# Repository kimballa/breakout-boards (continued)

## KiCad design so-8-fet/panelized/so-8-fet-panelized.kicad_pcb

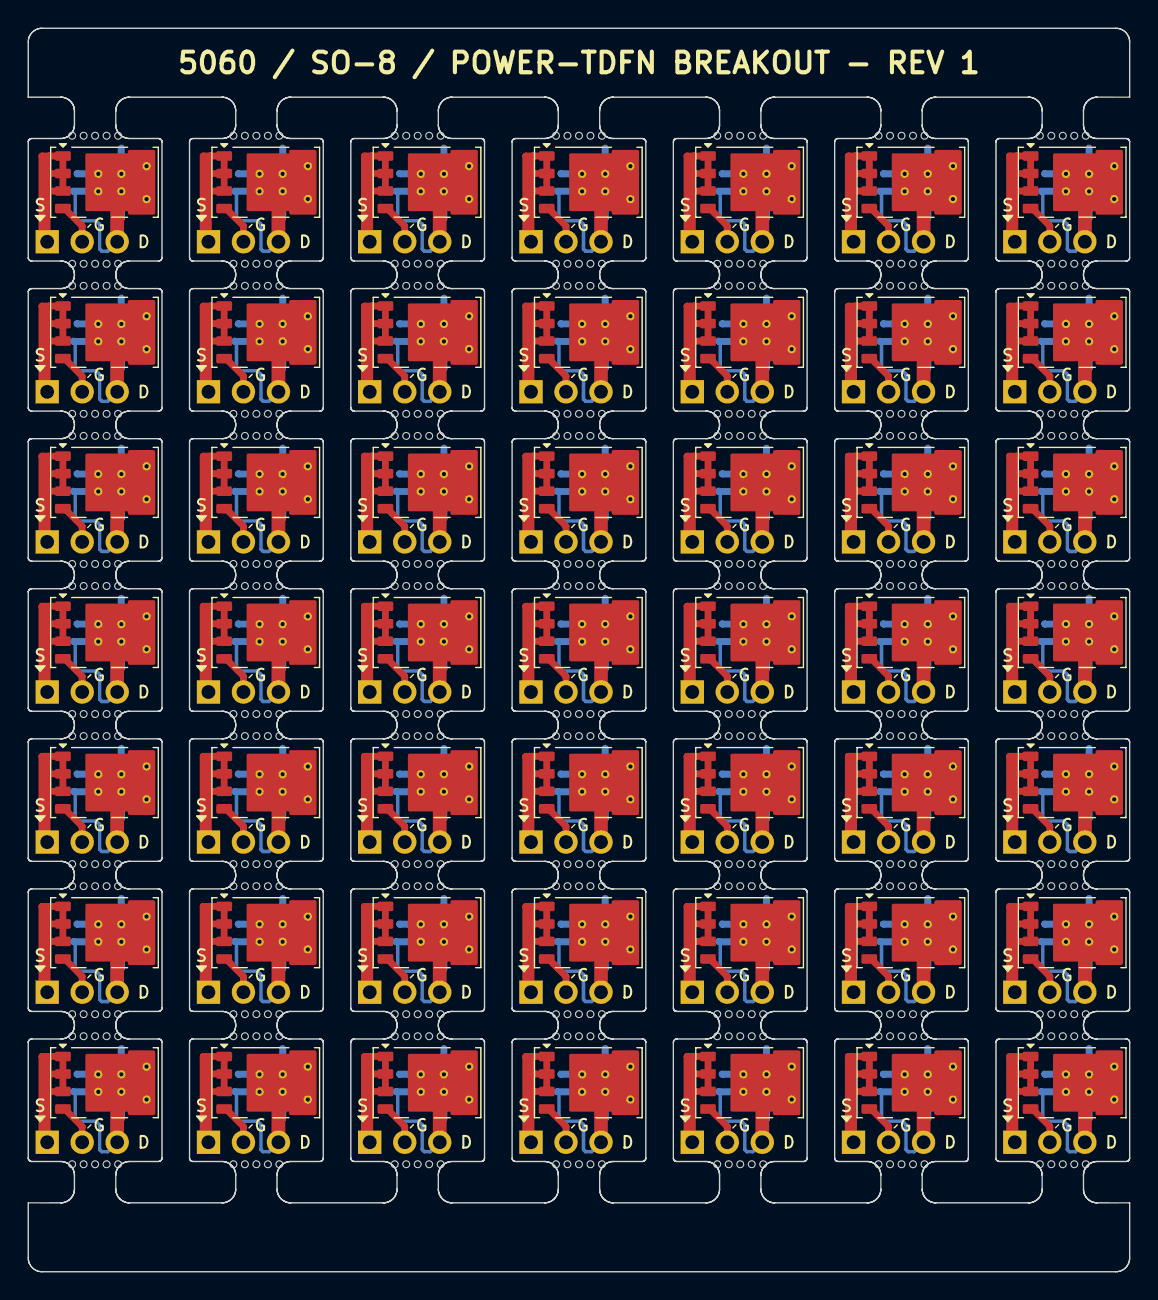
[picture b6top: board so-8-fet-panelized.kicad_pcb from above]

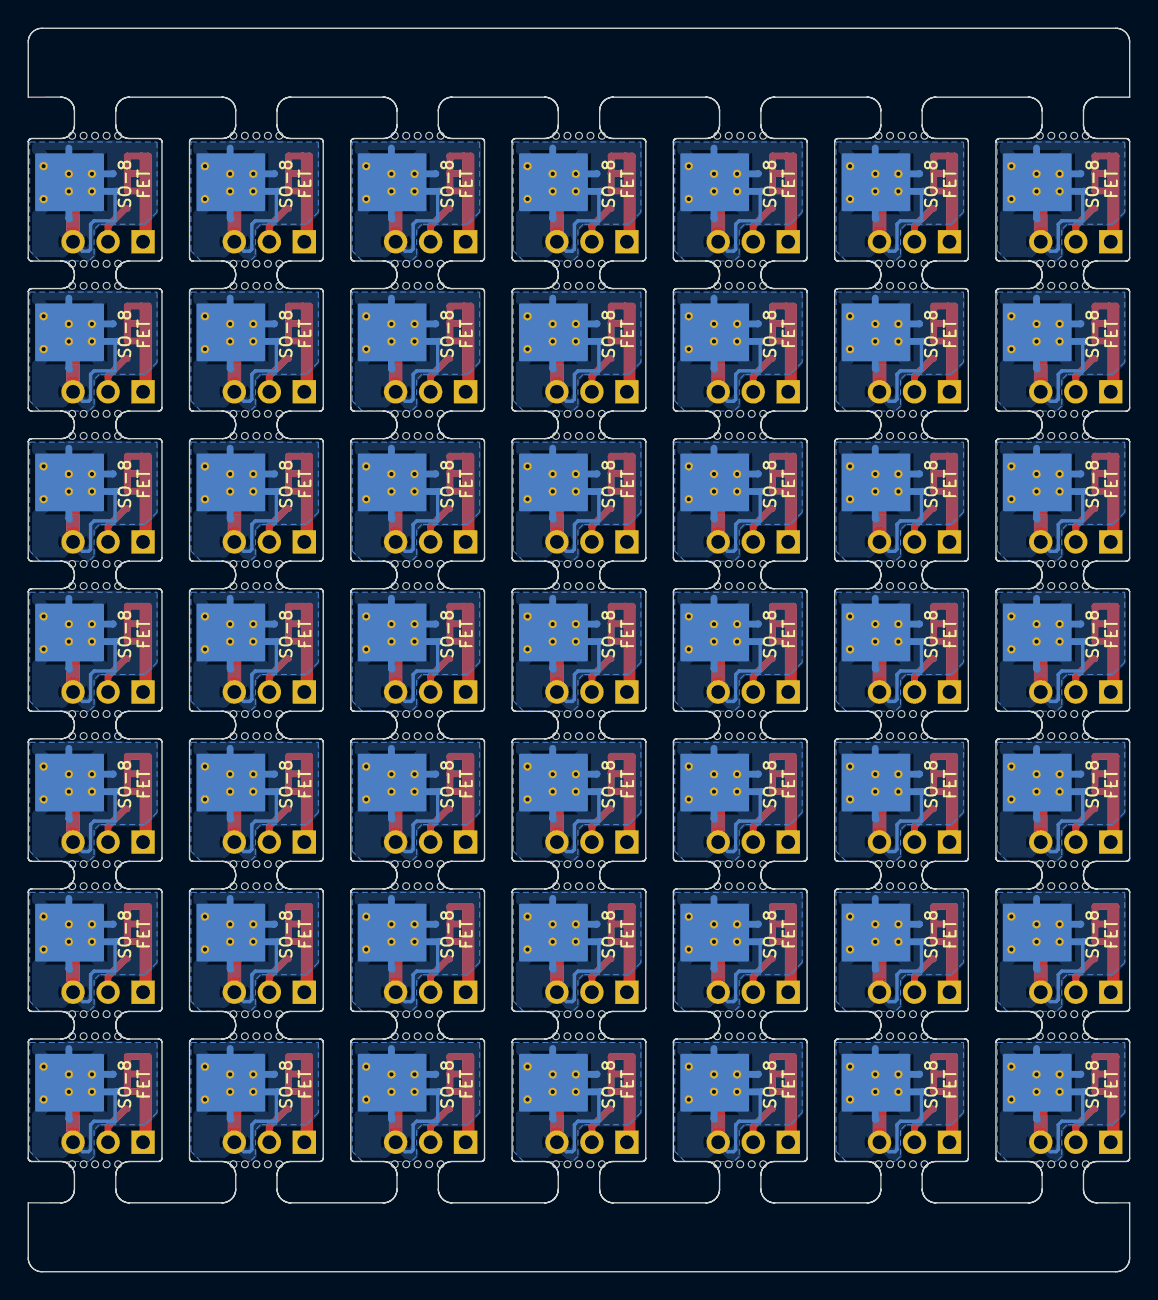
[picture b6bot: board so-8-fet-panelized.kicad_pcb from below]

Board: 2 copper layers, 79.9 x 90.2 mm, 588 parts (49 on the bottom side), 147 nets.

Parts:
J1, J1#2, J1#3, J1#4, J1#5, J1#6, J1#7, J1#8, J1#9, J1#10, J1#11, J1#12, J1#13, J1#14, J1#15, J1#16, J1#17, J1#18, J1#19, J1#20, J1#21, J1#22, J1#23, J1#24, J1#25, J1#26, J1#27, J1#28, J1#29, J1#30, J1#31, J1#32, J1#33, J1#34, J1#35, J1#36, J1#37, J1#38, J1#39, J1#40, J1#41, J1#42, J1#43, J1#44, J1#45, J1#46, J1#47, J1#48, J1#49: Conn_01x03; PinHeader_1x03_P2.54mm_Vertical
KiKit_MB_1_2, KiKit_MB_1_3, KiKit_MB_1_4, KiKit_MB_1_5, KiKit_MB_1_6, KiKit_MB_2_2, KiKit_MB_2_3, KiKit_MB_2_4, KiKit_MB_2_5, KiKit_MB_2_6, KiKit_MB_3_2, KiKit_MB_3_3, KiKit_MB_3_4, KiKit_MB_3_5, KiKit_MB_3_6, KiKit_MB_4_2, KiKit_MB_4_3, KiKit_MB_4_4, KiKit_MB_4_5, KiKit_MB_4_6, KiKit_MB_5_2, KiKit_MB_5_3, KiKit_MB_5_4, KiKit_MB_5_5, KiKit_MB_5_6, KiKit_MB_6_2, KiKit_MB_6_3, KiKit_MB_6_4, KiKit_MB_6_5, KiKit_MB_6_6, KiKit_MB_7_2, KiKit_MB_7_3, KiKit_MB_7_4, KiKit_MB_7_5, KiKit_MB_7_6, KiKit_MB_8_2, KiKit_MB_8_3, KiKit_MB_8_4, KiKit_MB_8_5, KiKit_MB_8_6, KiKit_MB_9_2, KiKit_MB_9_3, KiKit_MB_9_4, KiKit_MB_9_5, KiKit_MB_9_6, KiKit_MB_10_2, KiKit_MB_10_3, KiKit_MB_10_4, KiKit_MB_10_5, KiKit_MB_10_6, KiKit_MB_11_2, KiKit_MB_11_3, KiKit_MB_11_4, KiKit_MB_11_5, KiKit_MB_11_6, KiKit_MB_12_2, KiKit_MB_12_3, KiKit_MB_12_4, KiKit_MB_12_5, KiKit_MB_12_6, KiKit_MB_13_2, KiKit_MB_13_3, KiKit_MB_13_4, KiKit_MB_13_5, KiKit_MB_13_6, KiKit_MB_14_2, KiKit_MB_14_3, KiKit_MB_14_4, KiKit_MB_14_5, KiKit_MB_14_6, KiKit_MB_15_2, KiKit_MB_15_3, KiKit_MB_15_4, KiKit_MB_15_5, KiKit_MB_15_6, KiKit_MB_16_2, KiKit_MB_16_3, KiKit_MB_16_4, KiKit_MB_16_5, KiKit_MB_16_6, KiKit_MB_17_2, KiKit_MB_17_3, KiKit_MB_17_4, KiKit_MB_17_5, KiKit_MB_17_6, KiKit_MB_18_2, KiKit_MB_18_3, KiKit_MB_18_4, KiKit_MB_18_5, KiKit_MB_18_6, KiKit_MB_19_2, KiKit_MB_19_3, KiKit_MB_19_4, KiKit_MB_19_5, KiKit_MB_19_6, KiKit_MB_20_2, KiKit_MB_20_3, KiKit_MB_20_4, KiKit_MB_20_5, KiKit_MB_20_6, KiKit_MB_21_2, KiKit_MB_21_3, KiKit_MB_21_4, KiKit_MB_21_5, KiKit_MB_21_6, KiKit_MB_22_2, KiKit_MB_22_3, KiKit_MB_22_4, KiKit_MB_22_5, KiKit_MB_22_6, KiKit_MB_23_2, KiKit_MB_23_3, KiKit_MB_23_4, KiKit_MB_23_5, KiKit_MB_23_6, KiKit_MB_24_2, KiKit_MB_24_3, KiKit_MB_24_4, KiKit_MB_24_5, KiKit_MB_24_6, KiKit_MB_25_2, KiKit_MB_25_3, KiKit_MB_25_4, KiKit_MB_25_5, KiKit_MB_25_6, KiKit_MB_26_2, KiKit_MB_26_3, KiKit_MB_26_4, KiKit_MB_26_5, KiKit_MB_26_6, KiKit_MB_27_2, KiKit_MB_27_3, KiKit_MB_27_4, KiKit_MB_27_5, KiKit_MB_27_6, KiKit_MB_28_2, KiKit_MB_28_3, KiKit_MB_28_4, KiKit_MB_28_5, KiKit_MB_28_6, KiKit_MB_29_2, KiKit_MB_29_3, KiKit_MB_29_4, KiKit_MB_29_5, KiKit_MB_29_6, KiKit_MB_30_2, KiKit_MB_30_3, KiKit_MB_30_4, KiKit_MB_30_5, KiKit_MB_30_6, KiKit_MB_31_2, KiKit_MB_31_3, KiKit_MB_31_4, KiKit_MB_31_5, KiKit_MB_31_6, KiKit_MB_32_2, KiKit_MB_32_3, KiKit_MB_32_4, KiKit_MB_32_5, KiKit_MB_32_6, KiKit_MB_33_2, KiKit_MB_33_3, KiKit_MB_33_4, KiKit_MB_33_5, KiKit_MB_33_6, KiKit_MB_34_2, KiKit_MB_34_3, KiKit_MB_34_4, KiKit_MB_34_5, KiKit_MB_34_6, KiKit_MB_35_2, KiKit_MB_35_3, KiKit_MB_35_4, KiKit_MB_35_5, KiKit_MB_35_6, KiKit_MB_36_2, KiKit_MB_36_3, KiKit_MB_36_4, KiKit_MB_36_5, KiKit_MB_36_6, KiKit_MB_37_2, KiKit_MB_37_3, KiKit_MB_37_4, KiKit_MB_37_5, KiKit_MB_37_6, KiKit_MB_38_2, KiKit_MB_38_3, KiKit_MB_38_4, KiKit_MB_38_5, KiKit_MB_38_6, KiKit_MB_39_2, KiKit_MB_39_3, KiKit_MB_39_4, KiKit_MB_39_5, KiKit_MB_39_6, KiKit_MB_40_2, KiKit_MB_40_3, KiKit_MB_40_4, KiKit_MB_40_5, KiKit_MB_40_6, KiKit_MB_41_2, KiKit_MB_41_3, KiKit_MB_41_4, KiKit_MB_41_5, KiKit_MB_41_6, KiKit_MB_42_2, KiKit_MB_42_3, KiKit_MB_42_4, KiKit_MB_42_5, KiKit_MB_42_6, KiKit_MB_43_2, KiKit_MB_43_3, KiKit_MB_43_4, KiKit_MB_43_5, KiKit_MB_43_6, KiKit_MB_44_2, KiKit_MB_44_3, KiKit_MB_44_4, KiKit_MB_44_5, KiKit_MB_44_6, KiKit_MB_45_2, KiKit_MB_45_3, KiKit_MB_45_4, KiKit_MB_45_5, KiKit_MB_45_6, KiKit_MB_46_2, KiKit_MB_46_3, KiKit_MB_46_4, KiKit_MB_46_5, KiKit_MB_46_6, KiKit_MB_47_2, KiKit_MB_47_3, KiKit_MB_47_4, KiKit_MB_47_5, KiKit_MB_47_6, KiKit_MB_48_2, KiKit_MB_48_3, KiKit_MB_48_4, KiKit_MB_48_5, KiKit_MB_48_6, KiKit_MB_49_2, KiKit_MB_49_3, KiKit_MB_49_4, KiKit_MB_49_5, KiKit_MB_49_6, KiKit_MB_50_2, KiKit_MB_50_3, KiKit_MB_50_4, KiKit_MB_50_5, KiKit_MB_50_6, KiKit_MB_51_2, KiKit_MB_51_3, KiKit_MB_51_4, KiKit_MB_51_5, KiKit_MB_51_6, KiKit_MB_52_2, KiKit_MB_52_3, KiKit_MB_52_4, KiKit_MB_52_5, KiKit_MB_52_6, KiKit_MB_53_2, KiKit_MB_53_3, KiKit_MB_53_4, KiKit_MB_53_5, KiKit_MB_53_6, KiKit_MB_54_2, KiKit_MB_54_3, KiKit_MB_54_4, KiKit_MB_54_5, KiKit_MB_54_6, KiKit_MB_55_2, KiKit_MB_55_3, KiKit_MB_55_4, KiKit_MB_55_5, KiKit_MB_55_6, KiKit_MB_56_2, KiKit_MB_56_3, KiKit_MB_56_4, KiKit_MB_56_5, KiKit_MB_56_6, KiKit_MB_57_2, KiKit_MB_57_3, KiKit_MB_57_4, KiKit_MB_57_5, KiKit_MB_57_6, KiKit_MB_58_2, KiKit_MB_58_3, KiKit_MB_58_4, KiKit_MB_58_5, KiKit_MB_58_6, KiKit_MB_59_2, KiKit_MB_59_3, KiKit_MB_59_4, KiKit_MB_59_5, KiKit_MB_59_6, KiKit_MB_60_2, KiKit_MB_60_3, KiKit_MB_60_4, KiKit_MB_60_5, KiKit_MB_60_6, KiKit_MB_61_2, KiKit_MB_61_3, KiKit_MB_61_4, KiKit_MB_61_5, KiKit_MB_61_6, KiKit_MB_62_2, KiKit_MB_62_3, KiKit_MB_62_4, KiKit_MB_62_5, KiKit_MB_62_6, KiKit_MB_63_2, KiKit_MB_63_3, KiKit_MB_63_4, KiKit_MB_63_5, KiKit_MB_63_6, KiKit_MB_64_2, KiKit_MB_64_3, KiKit_MB_64_4, KiKit_MB_64_5, KiKit_MB_64_6, KiKit_MB_65_2, KiKit_MB_65_3, KiKit_MB_65_4, KiKit_MB_65_5, KiKit_MB_65_6, KiKit_MB_66_2, KiKit_MB_66_3, KiKit_MB_66_4, KiKit_MB_66_5, KiKit_MB_66_6, KiKit_MB_67_2, KiKit_MB_67_3, KiKit_MB_67_4, KiKit_MB_67_5, KiKit_MB_67_6, KiKit_MB_68_2, KiKit_MB_68_3, KiKit_MB_68_4, KiKit_MB_68_5, KiKit_MB_68_6, KiKit_MB_69_2, KiKit_MB_69_3, KiKit_MB_69_4, KiKit_MB_69_5, KiKit_MB_69_6, KiKit_MB_70_2, KiKit_MB_70_3, KiKit_MB_70_4, KiKit_MB_70_5, KiKit_MB_70_6, KiKit_MB_71_2, KiKit_MB_71_3, KiKit_MB_71_4, KiKit_MB_71_5, KiKit_MB_71_6, KiKit_MB_72_2, KiKit_MB_72_3, KiKit_MB_72_4, KiKit_MB_72_5, KiKit_MB_72_6, KiKit_MB_73_2, KiKit_MB_73_3, KiKit_MB_73_4, KiKit_MB_73_5, KiKit_MB_73_6, KiKit_MB_74_2, KiKit_MB_74_3, KiKit_MB_74_4, KiKit_MB_74_5, KiKit_MB_74_6, KiKit_MB_75_2, KiKit_MB_75_3, KiKit_MB_75_4, KiKit_MB_75_5, KiKit_MB_75_6, KiKit_MB_76_2, KiKit_MB_76_3, KiKit_MB_76_4, KiKit_MB_76_5, KiKit_MB_76_6, KiKit_MB_77_2, KiKit_MB_77_3, KiKit_MB_77_4, KiKit_MB_77_5, KiKit_MB_77_6, KiKit_MB_78_2, KiKit_MB_78_3, KiKit_MB_78_4, KiKit_MB_78_5, KiKit_MB_78_6, KiKit_MB_79_2, KiKit_MB_79_3, KiKit_MB_79_4, KiKit_MB_79_5, KiKit_MB_79_6, KiKit_MB_80_2, KiKit_MB_80_3, KiKit_MB_80_4, KiKit_MB_80_5, KiKit_MB_80_6, KiKit_MB_81_2, KiKit_MB_81_3, KiKit_MB_81_4, KiKit_MB_81_5, KiKit_MB_81_6, KiKit_MB_82_2, KiKit_MB_82_3, KiKit_MB_82_4, KiKit_MB_82_5, KiKit_MB_82_6, KiKit_MB_83_2, KiKit_MB_83_3, KiKit_MB_83_4, KiKit_MB_83_5, KiKit_MB_83_6, KiKit_MB_84_2, KiKit_MB_84_3, KiKit_MB_84_4, KiKit_MB_84_5, KiKit_MB_84_6, KiKit_MB_85_2, KiKit_MB_85_3, KiKit_MB_85_4, KiKit_MB_85_5, KiKit_MB_85_6, KiKit_MB_86_2, KiKit_MB_86_3, KiKit_MB_86_4, KiKit_MB_86_5, KiKit_MB_86_6, KiKit_MB_87_2, KiKit_MB_87_3, KiKit_MB_87_4, KiKit_MB_87_5, KiKit_MB_87_6, KiKit_MB_88_2, KiKit_MB_88_3, KiKit_MB_88_4, KiKit_MB_88_5, KiKit_MB_88_6, KiKit_MB_89_2, KiKit_MB_89_3, KiKit_MB_89_4, KiKit_MB_89_5, KiKit_MB_89_6, KiKit_MB_90_2, KiKit_MB_90_3, KiKit_MB_90_4, KiKit_MB_90_5, KiKit_MB_90_6, KiKit_MB_91_2, KiKit_MB_91_3, KiKit_MB_91_4, KiKit_MB_91_5, KiKit_MB_91_6, KiKit_MB_92_2, KiKit_MB_92_3, KiKit_MB_92_4, KiKit_MB_92_5, KiKit_MB_92_6, KiKit_MB_93_2, KiKit_MB_93_3, KiKit_MB_93_4, KiKit_MB_93_5, KiKit_MB_93_6, KiKit_MB_94_2, KiKit_MB_94_3, KiKit_MB_94_4, KiKit_MB_94_5, KiKit_MB_94_6, KiKit_MB_95_2, KiKit_MB_95_3, KiKit_MB_95_4, KiKit_MB_95_5, KiKit_MB_95_6, KiKit_MB_96_2, KiKit_MB_96_3, KiKit_MB_96_4, KiKit_MB_96_5, KiKit_MB_96_6, KiKit_MB_97_2, KiKit_MB_97_3, KiKit_MB_97_4, KiKit_MB_97_5, KiKit_MB_97_6, KiKit_MB_98_2, KiKit_MB_98_3, KiKit_MB_98_4, KiKit_MB_98_5, KiKit_MB_98_6: NPTH
Q1, Q1#2, Q1#3, Q1#4, Q1#5, Q1#6, Q1#7, Q1#8, Q1#9, Q1#10, Q1#11, Q1#12, Q1#13, Q1#14, Q1#15, Q1#16, Q1#17, Q1#18, Q1#19, Q1#20, Q1#21, Q1#22, Q1#23, Q1#24, Q1#25, Q1#26, Q1#27, Q1#28, Q1#29, Q1#30, Q1#31, Q1#32, Q1#33, Q1#34, Q1#35, Q1#36, Q1#37, Q1#38, Q1#39, Q1#40, Q1#41, Q1#42, Q1#43, Q1#44, Q1#45, Q1#46, Q1#47, Q1#48, Q1#49: Q_NMOS_SSSGD_AvalancheRated; SO8_PowerTDFN_5x6_NXP_Universal_ThermalVias

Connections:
Board_0-/DRAIN: J1#33.3, Q1#29.5 (D)
Board_0-/GATE: J1#33.2, Q1#29.4 (G)
Board_0-/SRC: J1#33.1, Q1#29.1 (S), Q1#29.2 (S), Q1#29.3 (S)
Board_1-/DRAIN: J1#4.3, Q1#32.5 (D)
Board_1-/GATE: J1#4.2, Q1#32.4 (G)
Board_1-/SRC: J1#4.1, Q1#32.1 (S), Q1#32.2 (S), Q1#32.3 (S)
Board_2-/DRAIN: J1#30.3, Q1#39.5 (D)
Board_2-/GATE: J1#30.2, Q1#39.4 (G)
Board_2-/SRC: J1#30.1, Q1#39.1 (S), Q1#39.2 (S), Q1#39.3 (S)
Board_3-/DRAIN: J1#46.3, Q1#45.5 (D)
Board_3-/GATE: J1#46.2, Q1#45.4 (G)
Board_3-/SRC: J1#46.1, Q1#45.1 (S), Q1#45.2 (S), Q1#45.3 (S)
Board_4-/DRAIN: J1#20.3, Q1#31.5 (D)
Board_4-/GATE: J1#20.2, Q1#31.4 (G)
Board_4-/SRC: J1#20.1, Q1#31.1 (S), Q1#31.2 (S), Q1#31.3 (S)
Board_5-/DRAIN: J1#11.3, Q1#48.5 (D)
Board_5-/GATE: J1#11.2, Q1#48.4 (G)
Board_5-/SRC: J1#11.1, Q1#48.1 (S), Q1#48.2 (S), Q1#48.3 (S)
Board_6-/DRAIN: J1#7.3, Q1#35.5 (D)
Board_6-/GATE: J1#7.2, Q1#35.4 (G)
Board_6-/SRC: J1#7.1, Q1#35.1 (S), Q1#35.2 (S), Q1#35.3 (S)
Board_7-/DRAIN: J1#40.3, Q1#41.5 (D)
Board_7-/GATE: J1#40.2, Q1#41.4 (G)
Board_7-/SRC: J1#40.1, Q1#41.1 (S), Q1#41.2 (S), Q1#41.3 (S)
Board_8-/DRAIN: J1#10.3, Q1#6.5 (D)
Board_8-/GATE: J1#10.2, Q1#6.4 (G)
Board_8-/SRC: J1#10.1, Q1#6.1 (S), Q1#6.2 (S), Q1#6.3 (S)
Board_9-/DRAIN: J1#28.3, Q1#5.5 (D)
Board_9-/GATE: J1#28.2, Q1#5.4 (G)
Board_9-/SRC: J1#28.1, Q1#5.1 (S), Q1#5.2 (S), Q1#5.3 (S)
Board_10-/DRAIN: J1#45.3, Q1#21.5 (D)
Board_10-/GATE: J1#45.2, Q1#21.4 (G)
Board_10-/SRC: J1#45.1, Q1#21.1 (S), Q1#21.2 (S), Q1#21.3 (S)
Board_11-/DRAIN: J1#31.3, Q1#23.5 (D)
Board_11-/GATE: J1#31.2, Q1#23.4 (G)
Board_11-/SRC: J1#31.1, Q1#23.1 (S), Q1#23.2 (S), Q1#23.3 (S)
Board_12-/DRAIN: J1#29.3, Q1#12.5 (D)
Board_12-/GATE: J1#29.2, Q1#12.4 (G)
Board_12-/SRC: J1#29.1, Q1#12.1 (S), Q1#12.2 (S), Q1#12.3 (S)
Board_13-/DRAIN: J1#41.3, Q1#20.5 (D)
Board_13-/GATE: J1#41.2, Q1#20.4 (G)
Board_13-/SRC: J1#41.1, Q1#20.1 (S), Q1#20.2 (S), Q1#20.3 (S)
Board_14-/DRAIN: J1#15.3, Q1#9.5 (D)
Board_14-/GATE: J1#15.2, Q1#9.4 (G)
Board_14-/SRC: J1#15.1, Q1#9.1 (S), Q1#9.2 (S), Q1#9.3 (S)
Board_15-/DRAIN: J1#35.3, Q1#11.5 (D)
Board_15-/GATE: J1#35.2, Q1#11.4 (G)
Board_15-/SRC: J1#35.1, Q1#11.1 (S), Q1#11.2 (S), Q1#11.3 (S)
Board_16-/DRAIN: J1#5.3, Q1#10.5 (D)
Board_16-/GATE: J1#5.2, Q1#10.4 (G)
Board_16-/SRC: J1#5.1, Q1#10.1 (S), Q1#10.2 (S), Q1#10.3 (S)
Board_17-/DRAIN: J1#13.3, Q1#37.5 (D)
Board_17-/GATE: J1#13.2, Q1#37.4 (G)
Board_17-/SRC: J1#13.1, Q1#37.1 (S), Q1#37.2 (S), Q1#37.3 (S)
Board_18-/DRAIN: J1#24.3, Q1#40.5 (D)
Board_18-/GATE: J1#24.2, Q1#40.4 (G)
Board_18-/SRC: J1#24.1, Q1#40.1 (S), Q1#40.2 (S), Q1#40.3 (S)
Board_19-/DRAIN: J1#49.3, Q1#13.5 (D)
Board_19-/GATE: J1#49.2, Q1#13.4 (G)
Board_19-/SRC: J1#49.1, Q1#13.1 (S), Q1#13.2 (S), Q1#13.3 (S)
Board_20-/DRAIN: J1#26.3, Q1#22.5 (D)
Board_20-/GATE: J1#26.2, Q1#22.4 (G)
Board_20-/SRC: J1#26.1, Q1#22.1 (S), Q1#22.2 (S), Q1#22.3 (S)
Board_21-/DRAIN: J1.3, Q1#47.5 (D)
Board_21-/GATE: J1.2, Q1#47.4 (G)
Board_21-/SRC: J1.1, Q1#47.1 (S), Q1#47.2 (S), Q1#47.3 (S)
Board_22-/DRAIN: J1#23.3, Q1#3.5 (D)
Board_22-/GATE: J1#23.2, Q1#3.4 (G)
Board_22-/SRC: J1#23.1, Q1#3.1 (S), Q1#3.2 (S), Q1#3.3 (S)
Board_23-/DRAIN: J1#44.3, Q1#43.5 (D)
Board_23-/GATE: J1#44.2, Q1#43.4 (G)
Board_23-/SRC: J1#44.1, Q1#43.1 (S), Q1#43.2 (S), Q1#43.3 (S)
Board_24-/DRAIN: J1#12.3, Q1#19.5 (D)
Board_24-/GATE: J1#12.2, Q1#19.4 (G)
Board_24-/SRC: J1#12.1, Q1#19.1 (S), Q1#19.2 (S), Q1#19.3 (S)
Board_25-/DRAIN: J1#37.3, Q1#30.5 (D)
Board_25-/GATE: J1#37.2, Q1#30.4 (G)
Board_25-/SRC: J1#37.1, Q1#30.1 (S), Q1#30.2 (S), Q1#30.3 (S)
Board_26-/DRAIN: J1#47.3, Q1#46.5 (D)
Board_26-/GATE: J1#47.2, Q1#46.4 (G)
Board_26-/SRC: J1#47.1, Q1#46.1 (S), Q1#46.2 (S), Q1#46.3 (S)
Board_27-/DRAIN: J1#3.3, Q1#38.5 (D)
Board_27-/GATE: J1#3.2, Q1#38.4 (G)
Board_27-/SRC: J1#3.1, Q1#38.1 (S), Q1#38.2 (S), Q1#38.3 (S)
Board_28-/DRAIN: J1#36.3, Q1#33.5 (D)
Board_28-/GATE: J1#36.2, Q1#33.4 (G)
Board_28-/SRC: J1#36.1, Q1#33.1 (S), Q1#33.2 (S), Q1#33.3 (S)
Board_29-/DRAIN: J1#14.3, Q1#49.5 (D)
Board_29-/GATE: J1#14.2, Q1#49.4 (G)
Board_29-/SRC: J1#14.1, Q1#49.1 (S), Q1#49.2 (S), Q1#49.3 (S)
Board_30-/DRAIN: J1#38.3, Q1#34.5 (D)
Board_30-/GATE: J1#38.2, Q1#34.4 (G)
Board_30-/SRC: J1#38.1, Q1#34.1 (S), Q1#34.2 (S), Q1#34.3 (S)
Board_31-/DRAIN: J1#34.3, Q1#28.5 (D)
Board_31-/GATE: J1#34.2, Q1#28.4 (G)
Board_31-/SRC: J1#34.1, Q1#28.1 (S), Q1#28.2 (S), Q1#28.3 (S)
Board_32-/DRAIN: J1#2.3, Q1#7.5 (D)
Board_32-/GATE: J1#2.2, Q1#7.4 (G)
Board_32-/SRC: J1#2.1, Q1#7.1 (S), Q1#7.2 (S), Q1#7.3 (S)
Board_33-/DRAIN: J1#42.3, Q1#8.5 (D)
Board_33-/GATE: J1#42.2, Q1#8.4 (G)
Board_33-/SRC: J1#42.1, Q1#8.1 (S), Q1#8.2 (S), Q1#8.3 (S)
Board_34-/DRAIN: J1#19.3, Q1#25.5 (D)
Board_34-/GATE: J1#19.2, Q1#25.4 (G)
Board_34-/SRC: J1#19.1, Q1#25.1 (S), Q1#25.2 (S), Q1#25.3 (S)
Board_35-/DRAIN: J1#27.3, Q1.5 (D)
Board_35-/GATE: J1#27.2, Q1.4 (G)
Board_35-/SRC: J1#27.1, Q1.1 (S), Q1.2 (S), Q1.3 (S)
Board_36-/DRAIN: J1#25.3, Q1#18.5 (D)
Board_36-/GATE: J1#25.2, Q1#18.4 (G)
Board_36-/SRC: J1#25.1, Q1#18.1 (S), Q1#18.2 (S), Q1#18.3 (S)
Board_37-/DRAIN: J1#43.3, Q1#2.5 (D)
Board_37-/GATE: J1#43.2, Q1#2.4 (G)
Board_37-/SRC: J1#43.1, Q1#2.1 (S), Q1#2.2 (S), Q1#2.3 (S)
Board_38-/DRAIN: J1#8.3, Q1#24.5 (D)
Board_38-/GATE: J1#8.2, Q1#24.4 (G)
Board_38-/SRC: J1#8.1, Q1#24.1 (S), Q1#24.2 (S), Q1#24.3 (S)
Board_39-/DRAIN: J1#18.3, Q1#44.5 (D)
Board_39-/GATE: J1#18.2, Q1#44.4 (G)
Board_39-/SRC: J1#18.1, Q1#44.1 (S), Q1#44.2 (S), Q1#44.3 (S)
Board_40-/DRAIN: J1#6.3, Q1#16.5 (D)
Board_40-/GATE: J1#6.2, Q1#16.4 (G)
Board_40-/SRC: J1#6.1, Q1#16.1 (S), Q1#16.2 (S), Q1#16.3 (S)
Board_41-/DRAIN: J1#21.3, Q1#17.5 (D)
Board_41-/GATE: J1#21.2, Q1#17.4 (G)
Board_41-/SRC: J1#21.1, Q1#17.1 (S), Q1#17.2 (S), Q1#17.3 (S)
Board_42-/DRAIN: J1#32.3, Q1#36.5 (D)
Board_42-/GATE: J1#32.2, Q1#36.4 (G)
Board_42-/SRC: J1#32.1, Q1#36.1 (S), Q1#36.2 (S), Q1#36.3 (S)
Board_43-/DRAIN: J1#9.3, Q1#27.5 (D)
Board_43-/GATE: J1#9.2, Q1#27.4 (G)
Board_43-/SRC: J1#9.1, Q1#27.1 (S), Q1#27.2 (S), Q1#27.3 (S)
Board_44-/DRAIN: J1#39.3, Q1#42.5 (D)
Board_44-/GATE: J1#39.2, Q1#42.4 (G)
Board_44-/SRC: J1#39.1, Q1#42.1 (S), Q1#42.2 (S), Q1#42.3 (S)
Board_45-/DRAIN: J1#48.3, Q1#15.5 (D)
Board_45-/GATE: J1#48.2, Q1#15.4 (G)
Board_45-/SRC: J1#48.1, Q1#15.1 (S), Q1#15.2 (S), Q1#15.3 (S)
Board_46-/DRAIN: J1#22.3, Q1#14.5 (D)
Board_46-/GATE: J1#22.2, Q1#14.4 (G)
Board_46-/SRC: J1#22.1, Q1#14.1 (S), Q1#14.2 (S), Q1#14.3 (S)
Board_47-/DRAIN: J1#17.3, Q1#26.5 (D)
Board_47-/GATE: J1#17.2, Q1#26.4 (G)
Board_47-/SRC: J1#17.1, Q1#26.1 (S), Q1#26.2 (S), Q1#26.3 (S)
Board_48-/DRAIN: J1#16.3, Q1#4.5 (D)
Board_48-/GATE: J1#16.2, Q1#4.4 (G)
Board_48-/SRC: J1#16.1, Q1#4.1 (S), Q1#4.2 (S), Q1#4.3 (S)
